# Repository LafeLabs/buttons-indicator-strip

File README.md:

# buttons-indicator-strip
Modular system of buttons and indicators and Arduino shields

[https://www.mcmaster.com/90016A005/](https://www.mcmaster.com/90016A005/)

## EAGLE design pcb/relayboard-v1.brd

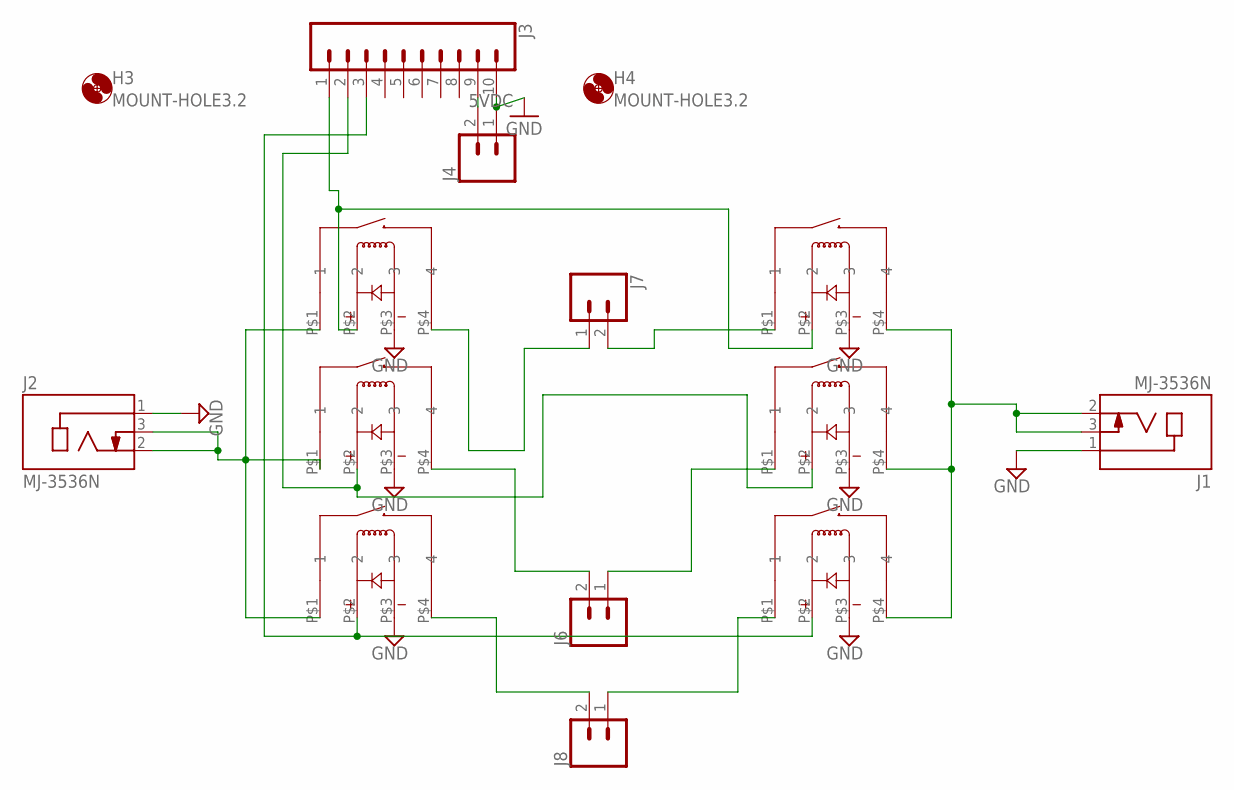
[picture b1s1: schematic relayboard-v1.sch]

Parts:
H3, H4: MOUNT-HOLE3.2; 3,2
J1, J2: MJ-3536N; CUI_MJ-3536N
J3: CONN_10"; 1X10
J4, J6, J7, J8: CONN_02; 1X02
U$3, U$4, U$5, U$6, U$7, U$8: RELAY-COMUS-3750-1331; RELAY-COMUS-3570-1331

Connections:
5VDC: J3.9, J4.2
GND: J1.1, J2.1, J3.10, J4.1, U$3.P$3 (3), U$4.P$3 (3), U$5.P$3 (3), U$6.P$3 (3), U$7.P$3 (3), U$8.P$3 (3)
unnamed: J2.2, J2.3, U$3.P$1 (1), U$5.P$1 (1), U$7.P$1 (1)
unnamed: J8.2, U$7.P$4 (4)
unnamed: J8.1, U$8.P$1 (1)
unnamed: J6.2, U$5.P$4 (4)
unnamed: J6.1, U$6.P$1 (1)
unnamed: J7.1, U$3.P$4 (4)
unnamed: J7.2, U$4.P$1 (1)
unnamed: J3.1, U$3.P$2 (2), U$4.P$2 (2)
unnamed: J3.3, U$7.P$2 (2), U$8.P$2 (2)
unnamed: J1.2, J1.3, U$4.P$4 (4), U$6.P$4 (4), U$8.P$4 (4)
unnamed: J3.2, U$5.P$2 (2), U$6.P$2 (2)

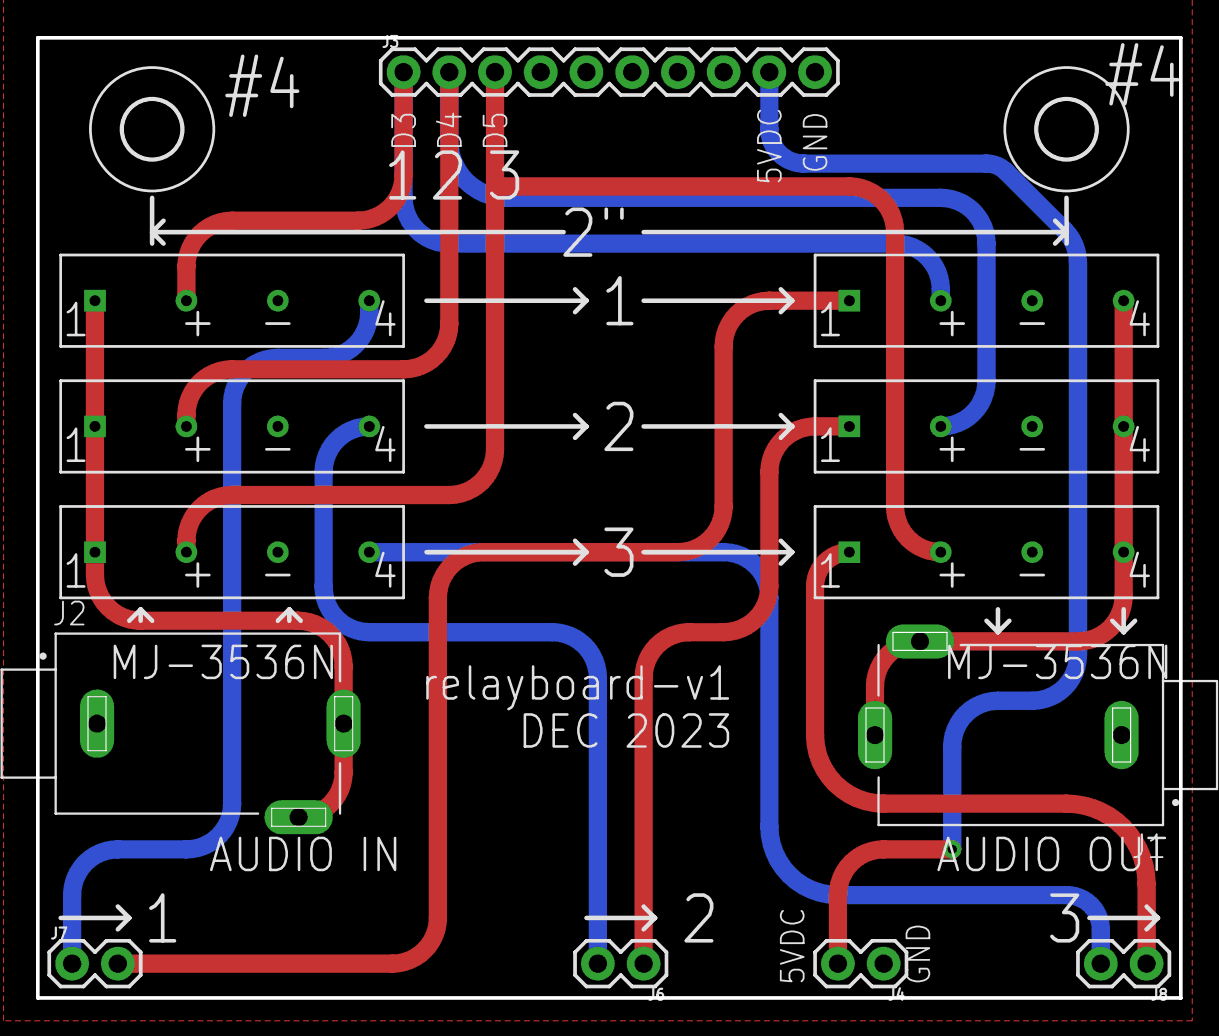
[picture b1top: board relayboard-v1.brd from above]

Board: 2 copper layers, 63.5 x 53.3 mm, 15 parts (0 on the bottom side), 13 nets.

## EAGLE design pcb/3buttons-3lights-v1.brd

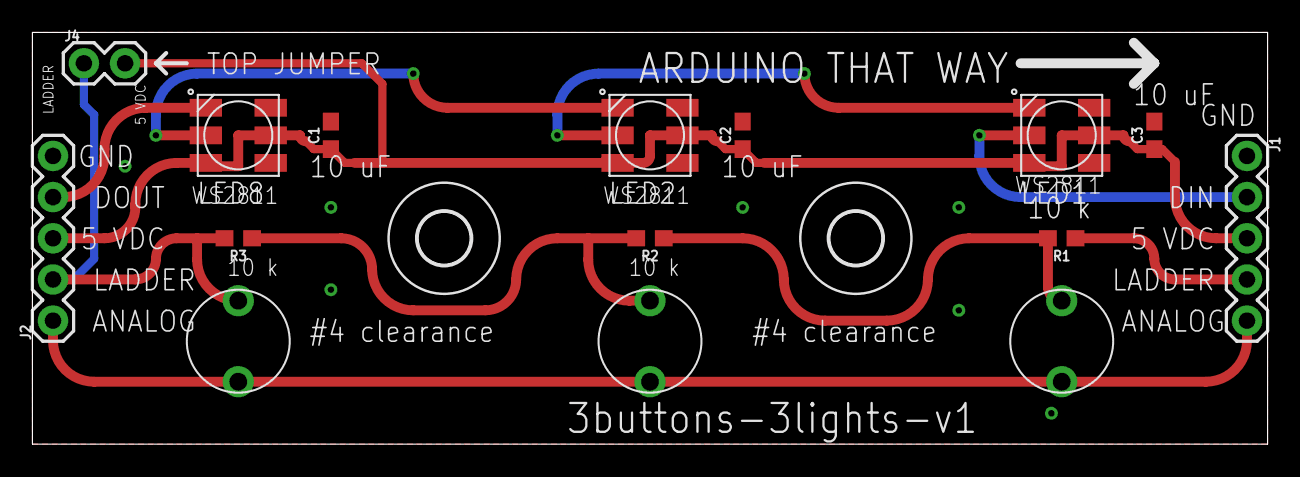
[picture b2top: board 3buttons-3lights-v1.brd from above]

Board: 2 copper layers, 76.2 x 25.4 mm, 17 parts (0 on the bottom side), 11 nets.

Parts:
C1, C2, C3: 10uF; 0603
H3, H4: MOUNT-HOLE3.2; 3,2
J1, J2: 1X05
J4: 1X02
LED1, LED2, LED8: WS28115050
R1, R2, R3: 10k; 0603
U$1, U$4, U$5: BUTTON

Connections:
+5V: C1.1, C2.1, C3.1, J1.3, J2.3, J4.2, LED1.LEDVDD, LED1.VDD, LED2.LEDVDD, LED2.VDD, LED8.LEDVDD, LED8.VDD
BUTTON: J1.5, J2.1, U$1.P$2, U$4.P$2, U$5.P$2
GND: C1.2, C2.2, C3.2, J1.1, J2.5, LED1.VSS, LED2.VSS, LED8.VSS
unnamed: LED1.DO, LED2.DI
unnamed: R1.2, R2.1, U$1.P$1
unnamed: R2.2, R3.1, U$4.P$1
unnamed: J2.2, J4.1, R3.2, U$5.P$1
unnamed: J1.4, R1.1
unnamed: LED2.DO, LED8.DI
unnamed: J1.2, LED1.DI
unnamed: J2.4, LED8.DO

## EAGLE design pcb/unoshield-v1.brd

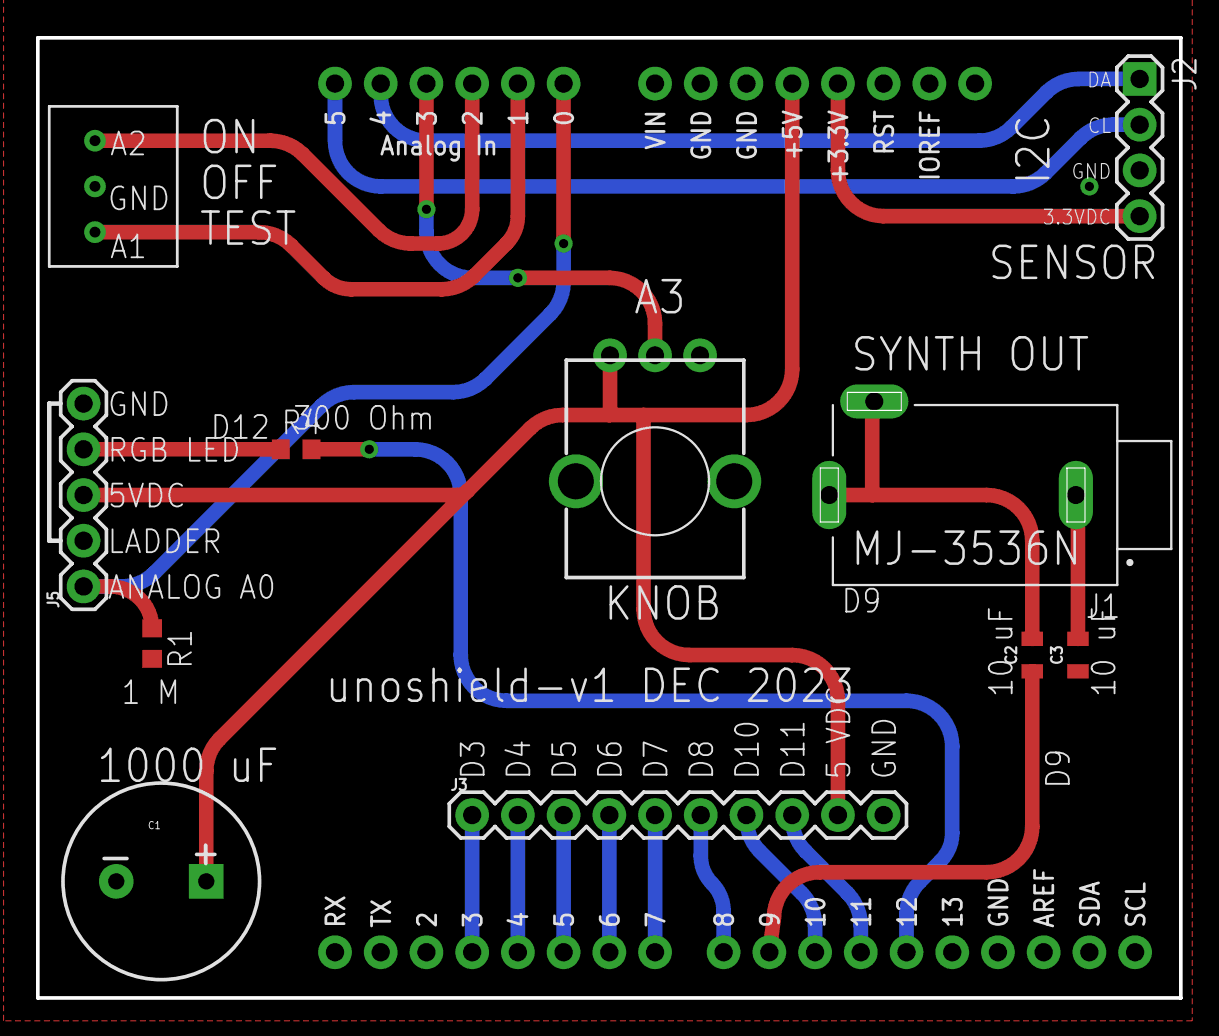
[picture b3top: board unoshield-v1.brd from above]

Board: 2 copper layers, 63.5 x 53.3 mm, 12 parts (0 on the bottom side), 22 nets.

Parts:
C1: 1000uf/25V; CPOL-RADIAL-1000UF-25V-KIT
C2, C3: 10uF; 0805
J1: MJ-3536N; CUI_MJ-3536N
J2: 1X04
J3: 1X10
J4: ARDUINO_R3_SHIELD; UNO_R3_SHIELD
J5: 1X05
R1: 1M; R0603
R4: 330; R0603
R5: 20k; ALPS_POT_KIT
SW3: ON-OFF-ON-360-1013-ND; 360-1013-ND

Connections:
5V: C1.+, J3.9, J4.5V, J5.3, R5.P$3
ANALOG: J4.A0, J5.1, R1.1
BUTTON: J4.A1, SW3.RIGHT
CL: J2.2, J4.A5
DA: J2.1, J4.A4
GND: C1.-, C3.1, J2.3, J3.10, J4.GND@0, J4.GND@1, J4.GND@2, J5.2, J5.5, R1.2, R5.P$1, SW3.CENTER
unnamed: J4.D12, R4.2
unnamed: J4.A3, R5.P$2
unnamed: J3.8, J4.D11
unnamed: J3.7, J4.D10
unnamed: J3.6, J4.D8
unnamed: J3.5, J4.D7
unnamed: J3.4, J4.D6
unnamed: J3.3, J4.D5
unnamed: J3.2, J4.D4
unnamed: J4.A2, SW3.LEFT
unnamed: J3.1, J4.D3
unnamed: C3.2, J1.1
unnamed: C2.2, J1.2, J1.3
unnamed: C2.1, J4.D9
unnamed: J5.4, R4.1
VCC: J2.4, J4.3.3V

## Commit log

2023-12-22 the boards are copied from another version
2023-12-23 2 boards are now close to ready
2023-12-24 designing circuit boards

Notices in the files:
parts and their libraries:
microbuilder: This work is placed in the public domain, and may be freely used for commercial and non-commercial work with the following conditions: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
SparkFun-Resistors: Licensing: Creative Commons ShareAlike 4.0 International - https://creativecommons.org/licenses/by-sa/4.0
